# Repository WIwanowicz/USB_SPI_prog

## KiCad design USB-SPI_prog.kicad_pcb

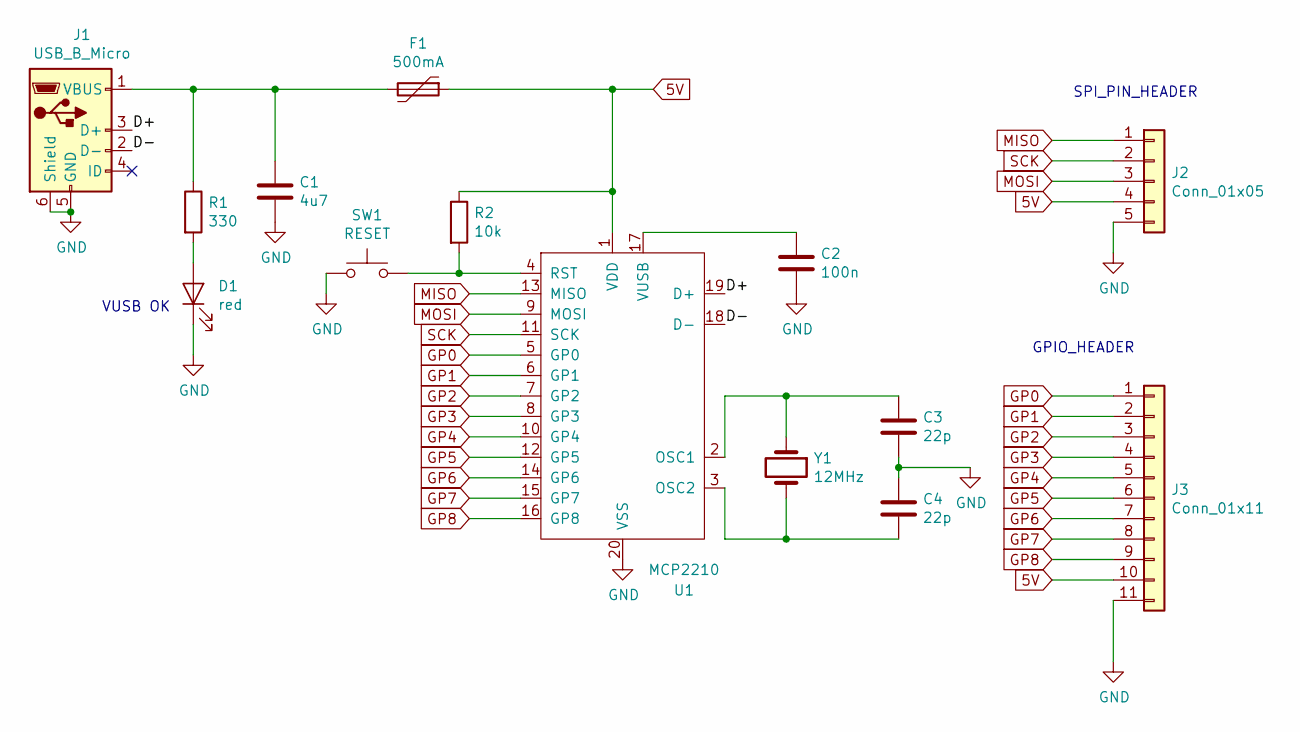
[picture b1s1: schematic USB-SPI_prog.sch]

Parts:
C1: 4u7; C_0805_2012Metric
C2: 100n; C_1206_3216Metric
C3, C4: 22p; C_0603_1608Metric
D1: red; LED_0603_1608Metric
F1: 500mA; Fuse_2920_7451Metric
J1: USB_B_Micro; USB_Micro-B_GCT_USB3076-30-A
J2: Conn_01x05; PinHeader_1x05_P2.54mm_Vertical
J3: Conn_01x11; PinHeader_1x11_P2.54mm_Vertical
R1: 330; R_0805_2012Metric
R2: 10k; R_0805_2012Metric
SW1: RESET; SW_MEC_5GSH9
U1: MCP2210; SOIC-20W_7.5x12.8mm_P1.27mm
Y1: 12MHz; Crystal_SMD_HC49-SD

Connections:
5V: F1.1, J2.4, J3.10, R2.1, U1.1 (VDD)
/D+: J1.3 (D+), U1.19 (D+)
/D-: J1.2 (D-), U1.18 (D-)
GND: C1.2, C2.2, C3.2, C4.1, D1.1 (K), J1.5 (GND), J1.6 (Shield), J2.5, J3.11, SW1.1, U1.20 (VSS)
GP0: J3.1, U1.5 (GP0)
GP1: J3.2, U1.6 (GP1)
GP2: J3.3, U1.7 (GP2)
GP3: J3.4, U1.8 (GP3)
GP4: J3.5, U1.10 (GP4)
GP5: J3.6, U1.12 (GP5)
GP6: J3.7, U1.14 (GP6)
GP7: J3.8, U1.15 (GP7)
GP8: J3.9, U1.16 (GP8)
MISO: J2.1, U1.13 (MISO)
MOSI: J2.3, U1.9 (MOSI)
unnamed: C1.1, F1.2, J1.1 (VBUS), R1.1
unnamed: C2.1, U1.17 (VUSB)
unnamed: C3.1, U1.2 (OSC1), Y1.1
unnamed: C4.2, U1.3 (OSC2), Y1.2
unnamed: D1.2 (A), R1.2
unnamed: R2.2, SW1.2, U1.4 (RST)
SCK: J2.2, U1.11 (SCK)

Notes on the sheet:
VUSB OK
SPI_PIN_HEADER
GPIO_HEADER

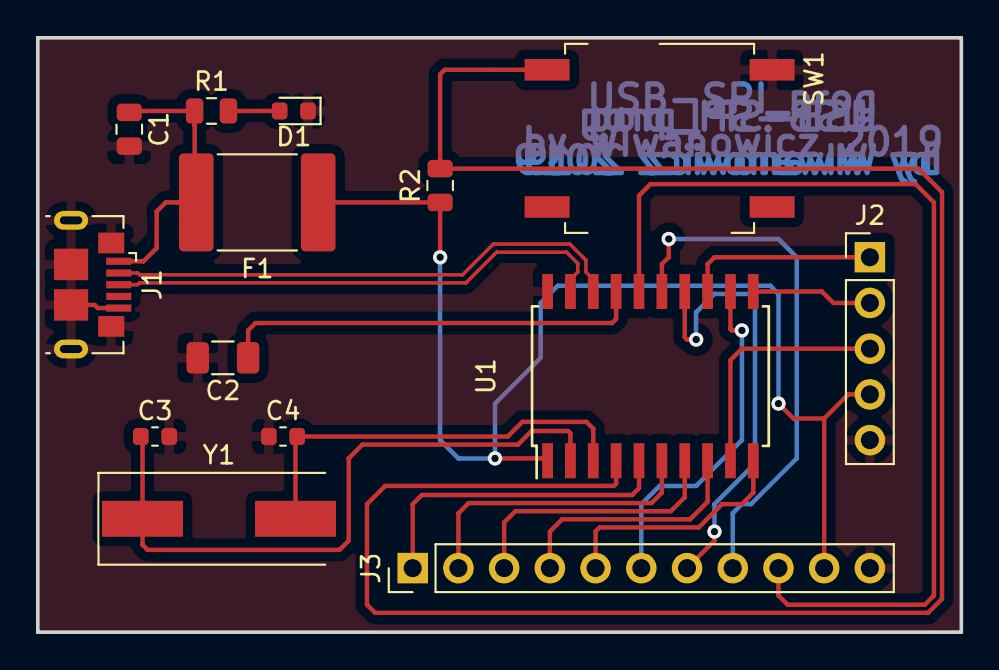
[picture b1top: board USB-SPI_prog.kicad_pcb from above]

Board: 2 copper layers, 51.3 x 33.0 mm, 14 parts (0 on the bottom side), 22 nets.

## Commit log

2019-09-24 USB-SPI_prog
    Simple USB to SPI converter. Could be used as AVR programmer.
